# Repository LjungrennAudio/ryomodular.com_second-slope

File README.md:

# ryomodular.com_second-slope
 a peak/trough-analog min/median/max module...

2408310019

this is a slightly interesting one - clearly this started as two separate module and then got cobbled together into abit of a monster but i suspect its got more legs yet and could really turn into something even more original and special.

it seems to consist of a min/median/max module - asolute classic analog logic tool a nd stalwart feature of any good patch programmable system - but nailed on the end is a peak/trough detector with a noice feature set of rising/falling/steady/moving outs.
it's definitely got legs as something but i'd like to find a away to make it far more unique and intersting than just plain old analog logic basics as is.
it's yet another candidate wth high possibilities as part of the jacob's ladder projecgt but i don't know if there's room fo all the functionality this offers in such a mdoule as that.

we'll have to watch and wait with baited breath, eh?

#######

2409060303

see jacob's ladder for continuation.

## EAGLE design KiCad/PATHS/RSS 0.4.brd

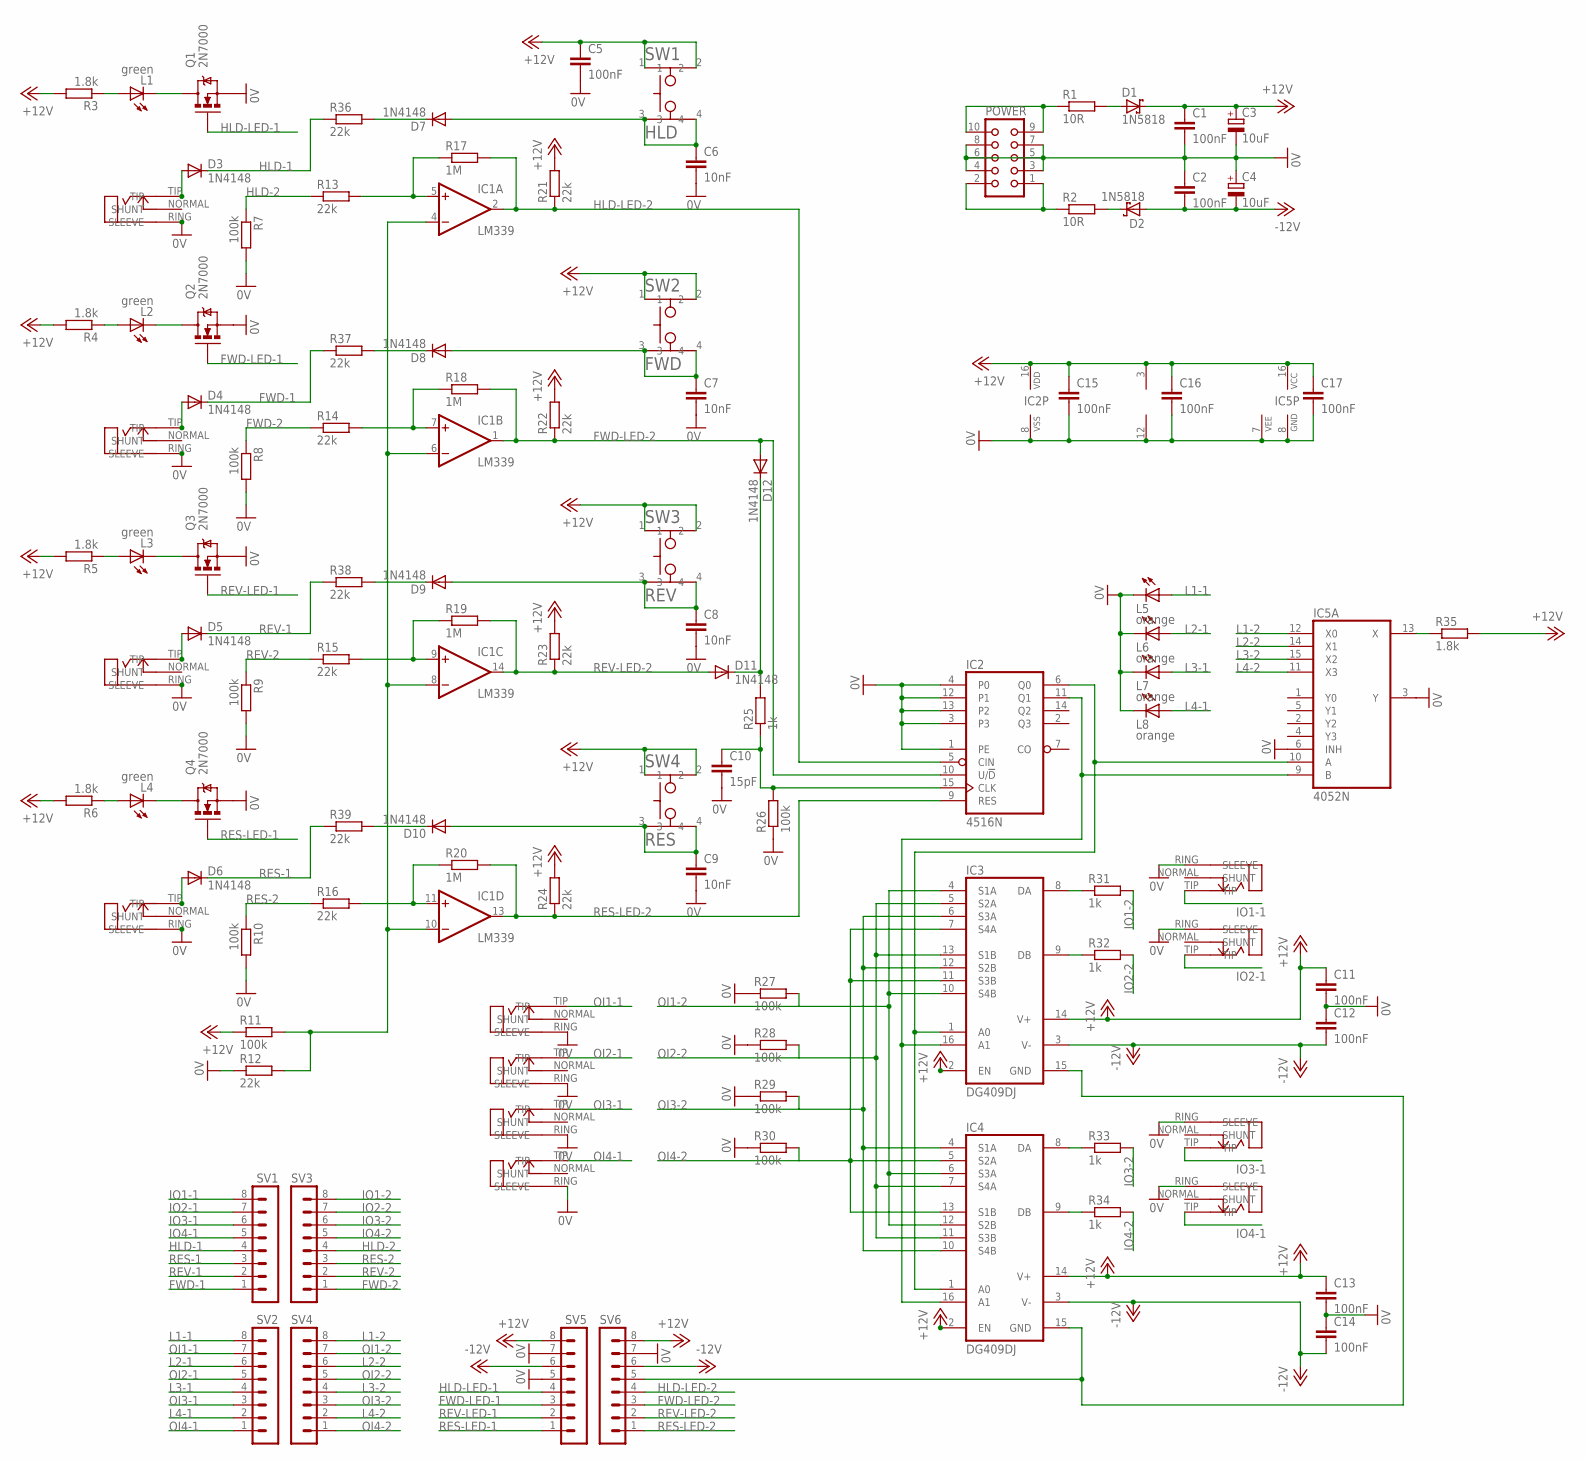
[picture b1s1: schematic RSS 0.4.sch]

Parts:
C1, C2, C5, C11, C12, C13, C14, C15, C16, C17: 100nF; C025-024X044
C3, C4: 10uF; E2-5
C6, C7, C8, C9: 10nF; C025-024X044
C10: 15pF; C025-024X044
D1, D2: 1N5818; DO41-7
D3, D4, D5, D6, D7, D8, D9, D10, D11, D12: 1N4148; DO35-7
FWD: ERTHENVAR_3.5MM_JACK; THONKICON
HLD: ERTHENVAR_3.5MM_JACK; THONKICON
I/O1, I/O2, I/O3, I/O4: ERTHENVAR_3.5MM_JACK; THONKICON
IC1: LM339; DIL14
IC2: 4516N; DIL16
IC3, IC4: DG409DJ; DIL16
IC5: 4052N; DIL16
L1, L2, L3, L4: green; LED3MM
L5, L6, L7, L8: orange; LED3MM
O/I1, O/I2, O/I3, O/I4: ERTHENVAR_3.5MM_JACK; THONKICON
POWER: CON10L
Q1, Q2, Q3, Q4: 2N7000; TO92-LINE
R1, R2: 10R; 0207/9
R3, R4, R5, R6, R35: 1.8k; 0207/9
R7, R8, R9, R10, R11, R26, R27, R28, R29, R30: 100k; 0207/9
R12, R13, R14, R15, R16, R21, R22, R23, R24, R36, R37, R38, R39: 22k; 0207/9
R17, R18, R19, R20: 1M; 0207/9
R25, R31, R32, R33, R34: 1k; 0207/9
RES: ERTHENVAR_3.5MM_JACK; THONKICON
REV: ERTHENVAR_3.5MM_JACK; THONKICON
SV1, SV2, SV3, SV4, SV5, SV6: MA08-1
SW1: HLD; TACTILE_ALPS
SW2: FWD; TACTILE_ALPS
SW3: REV; TACTILE_ALPS
SW4: RES; TACTILE_ALPS

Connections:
0V: C1.2, C2.1, C3.-, C4.+, C5.2, C6.2, C7.2, C8.2, C9.2, C10.2, C11.2, C12.1, C13.2, C14.1, C15.2, C16.2, C17.2, FWD.RING (SLEEVE), HLD.RING (SLEEVE), I/O1.RING (SLEEVE), I/O2.RING (SLEEVE), I/O3.RING (SLEEVE), I/O4.RING (SLEEVE), IC1.12 (V-), IC2.1 (PE), IC2.3, IC2.4 (P0), IC2.8 (VSS), IC2.12 (P1), IC2.13 (P2), IC5.3 (Y), IC5.6 (INH), IC5.7 (VEE), IC5.8 (GND), L5.K (C), L6.K (C), L7.K (C), L8.K (C), O/I1.RING (SLEEVE), O/I2.RING (SLEEVE), O/I3.RING (SLEEVE), O/I4.RING (SLEEVE), POWER.3, POWER.4, POWER.5, POWER.6, POWER.7, POWER.8, Q1.3 (S), Q2.3 (S), Q3.3 (S), Q4.3 (S), R7.2, R8.2, R9.2, R10.2, R12.1, R26.1, R27.1, R28.1, R29.1, R30.1, RES.RING (SLEEVE), REV.RING (SLEEVE), SV5.5, SV5.7, SV6.7
+12V: C1.1, C3.+, C5.1, C11.1, C13.1, C15.1, C16.1, C17.1, D1.C, IC1.3 (V+), IC2.16 (VDD), IC3.2 (EN), IC3.14 (V+), IC4.2 (EN), IC4.14 (V+), IC5.16 (VCC), R3.2, R4.2, R5.2, R6.2, R11.1, R21.2, R22.2, R23.2, R24.2, R35.2, SV5.8, SV6.8, SW1.1, SW1.2, SW2.1, SW2.2, SW3.1, SW3.2, SW4.1, SW4.2
-12V: C2.2, C4.-, C12.2, C14.2, D2.A, IC3.3 (V-), IC4.3 (V-), SV5.6, SV6.6
FWD-1: D4.C, R37.1, SV1.1
FWD-2: R8.1, R14.1, SV3.1
FWD-LED-1: Q2.2 (G), SV5.3
FWD-LED-2: D12.A, IC1.1 (OUT), IC2.10 (U/!D), R18.2, R22.1, SV6.3
HLD-1: D3.C, R36.1, SV1.4
HLD-2: R7.1, R13.1, SV3.4
HLD-LED-1: Q1.2 (G), SV5.4
HLD-LED-2: IC1.2 (OUT), IC2.5 (CIN), R17.2, R21.1, SV6.4
IO1-1: I/O1.TIP, SV1.8
IO1-2: R31.2, SV3.8
IO2-1: I/O2.TIP, SV1.7
IO2-2: R32.2, SV3.7
IO3-1: I/O3.TIP, SV1.6
IO3-2: R33.2, SV3.6
IO4-1: I/O4.TIP, SV1.5
IO4-2: R34.2, SV3.5
L1-1: L5.A, SV2.8
L1-2: IC5.12 (X0), SV4.8
L2-1: L6.A, SV2.6
L2-2: IC5.14 (X1), SV4.6
L3-1: L7.A, SV2.4
L3-2: IC5.15 (X2), SV4.4
L4-1: L8.A, SV2.2
L4-2: IC5.11 (X3), SV4.2
unnamed: IC2.11 (Q1), IC3.16 (A1), IC4.16 (A1), IC5.9 (B)
unnamed: IC2.6 (Q0), IC3.1 (A0), IC4.1 (A0), IC5.10 (A)
unnamed: IC3.15 (GND), IC4.15 (GND), SV6.5
unnamed: C10.1, IC2.15 (CLK), R25.1, R26.2
unnamed: IC3.9 (DB), R32.1
unnamed: IC4.9 (DB), R34.1
unnamed: L2.A, R4.1
unnamed: D3.A, HLD.TIP
unnamed: IC4.8 (DA), R33.1
unnamed: D4.A, FWD.TIP
unnamed: D5.A, REV.TIP
unnamed: D6.A, RES.TIP
unnamed: IC3.8 (DA), R31.1
unnamed: L2.K (C), Q2.1 (D)
unnamed: L3.A, R5.1
unnamed: C7.1, D8.A, SW2.3, SW2.4
unnamed: L3.K (C), Q3.1 (D)
unnamed: C6.1, D7.A, SW1.3, SW1.4
unnamed: IC5.13 (X), R35.1
unnamed: L4.A, R6.1
unnamed: IC1.7 (+IN), R14.2, R18.1
unnamed: POWER.1, POWER.2, R2.1
unnamed: POWER.9, POWER.10, R1.1
unnamed: D1.A, R1.2
unnamed: D2.C, R2.2
unnamed: IC1.5 (+IN), R13.2, R17.1
unnamed: IC1.9 (+IN), R15.2, R19.1
unnamed: L4.K (C), Q4.1 (D)
unnamed: IC1.4 (-IN), IC1.6 (-IN), IC1.8 (-IN), IC1.10 (-IN), R11.2, R12.2
unnamed: C8.1, D9.A, SW3.3, SW3.4
unnamed: IC1.11 (+IN), R16.2, R20.1
unnamed: C9.1, D10.A, SW4.3, SW4.4
unnamed: D10.C, R39.2
unnamed: D9.C, R38.2
unnamed: D8.C, R37.2
unnamed: D7.C, R36.2
unnamed: D11.C, D12.C, R25.2
unnamed: L1.A, R3.1
unnamed: L1.K (C), Q1.1 (D)
OI1-1: O/I1.TIP, SV2.7
OI1-2: IC3.4 (S1A), IC3.10 (S4B), IC4.6 (S3A), IC4.12 (S2B), R27.2, SV4.7
OI2-1: O/I2.TIP, SV2.5
OI2-2: IC3.5 (S2A), IC3.13 (S1B), IC4.7 (S4A), IC4.11 (S3B), R28.2, SV4.5
OI3-1: O/I3.TIP, SV2.3
OI3-2: IC3.6 (S3A), IC3.12 (S2B), IC4.4 (S1A), IC4.10 (S4B), R29.2, SV4.3
OI4-1: O/I4.TIP, SV2.1
OI4-2: IC3.7 (S4A), IC3.11 (S3B), IC4.5 (S2A), IC4.13 (S1B), R30.2, SV4.1
RES-1: D6.C, R39.1, SV1.3
RES-2: R10.1, R16.1, SV3.3
RES-LED-1: Q4.2 (G), SV5.1
RES-LED-2: IC1.13 (OUT), IC2.9 (RES), R20.2, R24.1, SV6.1
REV-1: D5.C, R38.1, SV1.2
REV-2: R9.1, R15.1, SV3.2
REV-LED-1: Q3.2 (G), SV5.2
REV-LED-2: D11.A, IC1.14 (OUT), R19.2, R23.1, SV6.2

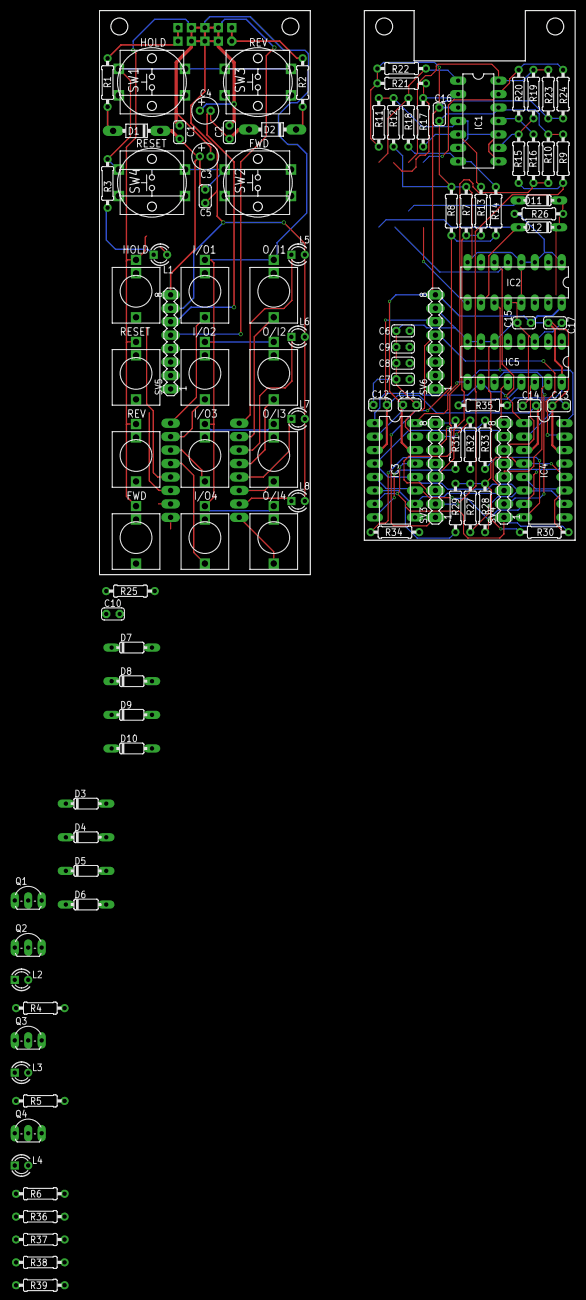
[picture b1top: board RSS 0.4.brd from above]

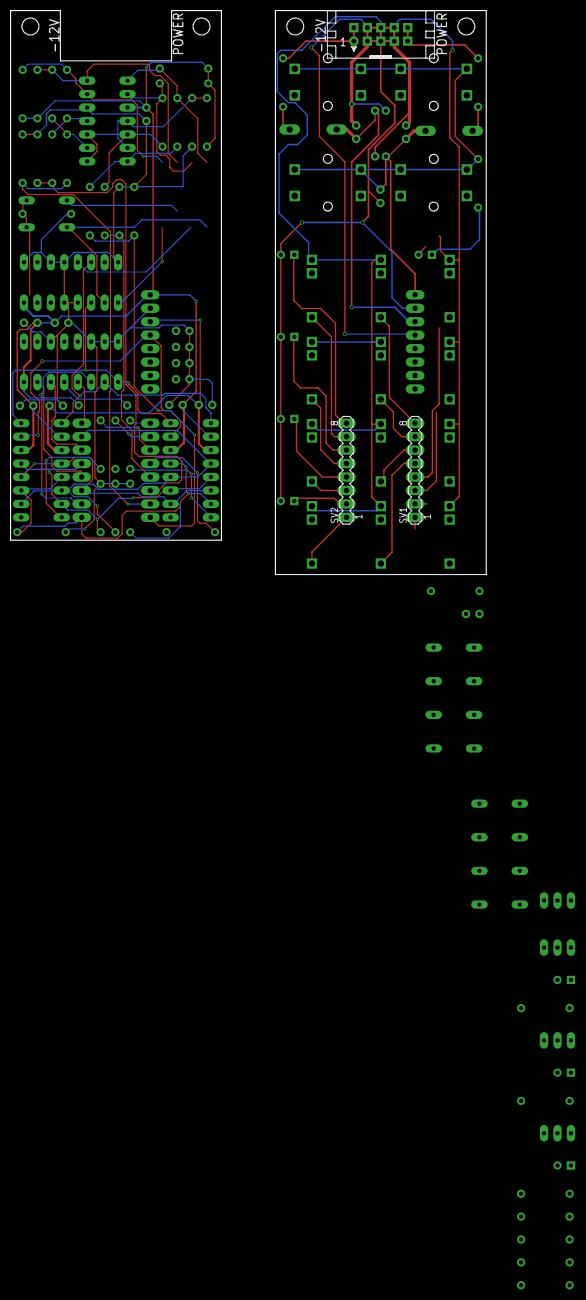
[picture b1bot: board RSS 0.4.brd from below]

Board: 2 copper layers, 89.8 x 106.5 mm, 108 parts (3 on the bottom side), 82 nets.

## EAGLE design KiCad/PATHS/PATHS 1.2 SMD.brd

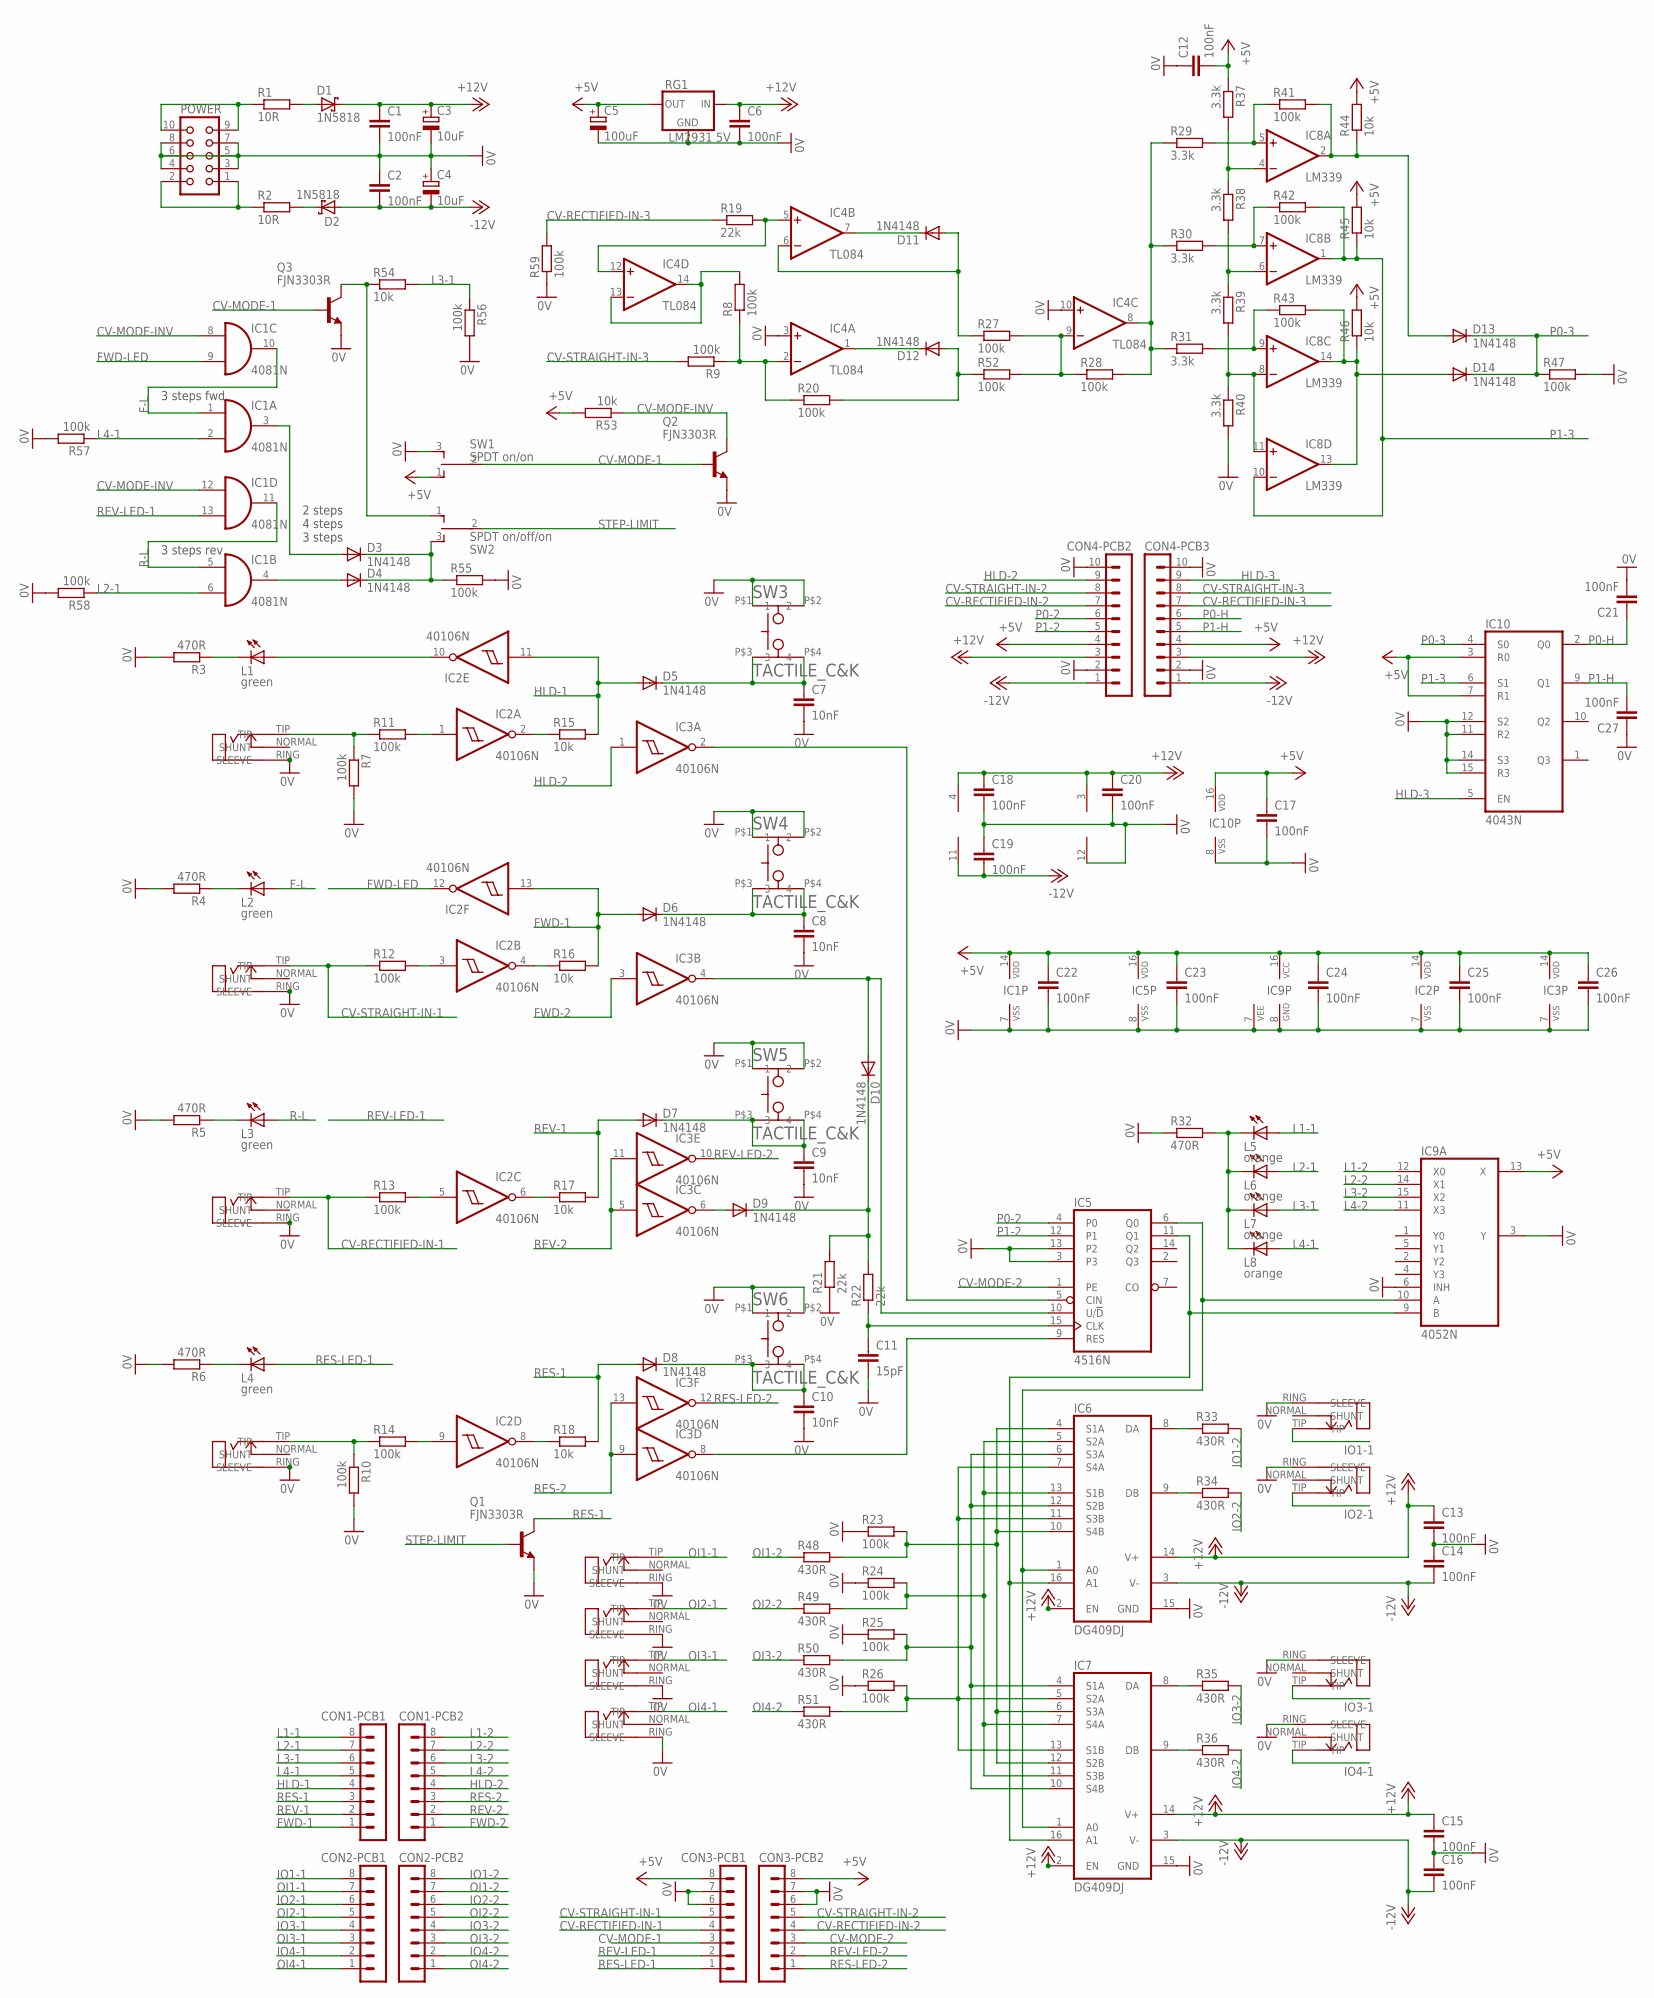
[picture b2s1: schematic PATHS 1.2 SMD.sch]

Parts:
C1, C2, C6, C12, C13, C14, C15, C16, C17, C18, C19, C20, C21, C22, C23, C24, C25, C26, C27: 100nF; C025-024X044
C3, C4: 10uF; E2-5
C5: 100uF; E2,5-6
C7, C8, C9, C10: 10nF; C025-024X044
C11: 15pF; C025-024X044
CON1-PCB1, CON1-PCB2, CON2-PCB1, CON2-PCB2, CON3-PCB1, CON3-PCB2: MA08-1
CON4-PCB2, CON4-PCB3: MA10-1
D1, D2: 1N5818; DO41-7
D3, D4, D5, D6, D7, D8, D9, D10, D11, D12, D13, D14: 1N4148; DO35-6
FWD: ERTHENVAR_3.5MM_JACKINLINE2; THONKICON-TWISTED
HLD: ERTHENVAR_3.5MM_JACKINLINE2; THONKICON-TWISTED
I/O1, I/O2, I/O3, I/O4: ERTHENVAR_3.5MM_JACKINLINE2; THONKICON-TWISTED
IC1: 4081N; DIL14
IC2, IC3: 40106N; DIL14
IC4: TL084; DIL14
IC5: 4516N; DIL16
IC6, IC7: DG409DJ; DIL16
IC8: LM339; DIL14
IC9: 4052N; DIL16
IC10: 4043N; DIL16
L1, L2, L3, L4: green; LED3MM
L5, L6, L7, L8: orange; LED3MM
O/I1, O/I2, O/I3, O/I4: ERTHENVAR_3.5MM_JACKINLINE2; THONKICON-TWISTED
POWER: CON10L
Q1, Q2, Q3: FJN3303R; TO92-LINE
R1, R2: 10R; 0207/9
R3, R4, R5, R6, R32: 470R; 0204/5
R7, R8, R9, R10, R11, R12, R13, R14, R20, R23, R24, R25, R26, R27, R28, R41, R42, R43, R47, R52, R55, R56, R57, R58, R59: 100k; 0204/5
R15, R16, R17, R18, R44, R45, R46, R53, R54: 10k; 0204/5
R19, R21, R22: 22k; 0204/5
R29, R30, R31, R37, R38, R39, R40: 3.3k; 0204/5
R33, R34, R35, R36, R48, R49, R50, R51: 430R; 0207/9
RES: ERTHENVAR_3.5MM_JACKINLINE2; THONKICON-TWISTED
REV: ERTHENVAR_3.5MM_JACKINLINE2; THONKICON-TWISTED
RG1: LM2931 5V; TO92-LINE
SW1: SPDT on/on; SPDT-HORIZONTAL-TOP-SUBMINI-MULTICOMP
SW2: SPDT on/off/on; SPDT-HORIZONTAL-TOP-SUBMINI-MULTICOMP
SW3, SW4, SW5, SW6: TACTILE_C&K; TACTILE_CK

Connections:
0V: C1.2, C2.1, C3.-, C4.+, C5.-, C6.2, C7.2, C8.2, C9.2, C10.2, C11.2, C12.1, C13.2, C14.1, C15.2, C16.1, C17.2, C18.2, C19.1, C20.2, C21.2, C22.2, C23.2, C24.2, C25.2, C26.2, C27.1, CON3-PCB1.6, CON3-PCB1.7, CON3-PCB2.6, CON3-PCB2.7, CON4-PCB2.2, CON4-PCB2.10, CON4-PCB3.2, CON4-PCB3.10, FWD.RING (SLEEVE), HLD.RING (SLEEVE), I/O1.RING (SLEEVE), I/O2.RING (SLEEVE), I/O3.RING (SLEEVE), I/O4.RING (SLEEVE), IC1.7 (VSS), IC2.7 (VSS), IC3.7 (VSS), IC4.3 (+IN), IC4.10 (+IN), IC5.3, IC5.8 (VSS), IC5.13 (P2), IC6.15 (GND), IC7.15 (GND), IC8.12 (V-), IC9.3 (Y), IC9.6 (INH), IC9.7 (VEE), IC9.8 (GND), IC10.8 (VSS), IC10.11 (R2), IC10.12 (S2), IC10.14 (S3), IC10.15 (R3), O/I1.RING (SLEEVE), O/I2.RING (SLEEVE), O/I3.RING (SLEEVE), O/I4.RING (SLEEVE), POWER.3, POWER.4, POWER.5, POWER.6, POWER.7, POWER.8, Q1.3 (E), Q2.3 (E), Q3.3 (E), R3.2, R4.2, R5.2, R6.2, R7.2, R10.2, R21.1, R23.1, R24.1, R25.1, R26.1, R32.1, R40.2, R47.2, R55.2, R56.2, R57.2, R58.2, R59.1, RES.RING (SLEEVE), REV.RING (SLEEVE), RG1.2 (GND), SW1.3, SW3.P$1 (1), SW3.P$2 (2), SW4.P$1 (1), SW4.P$2 (2), SW5.P$1 (1), SW5.P$2 (2), SW6.P$1 (1), SW6.P$2 (2)
+5V: C5.+, C12.2, C17.1, C22.1, C23.1, C24.1, C25.1, C26.1, CON3-PCB1.8, CON3-PCB2.8, CON4-PCB2.4, CON4-PCB3.4, IC1.14 (VDD), IC2.14 (VDD), IC3.14 (VDD), IC5.16 (VDD), IC9.13 (X), IC9.16 (VCC), IC10.3 (R0), IC10.7 (R1), IC10.16 (VDD), R37.1, R44.2, R45.2, R46.2, R53.2, RG1.3 (OUT), SW1.1
+12V: C1.1, C3.+, C6.1, C13.1, C15.1, C18.1, C20.1, CON4-PCB2.3, CON4-PCB3.3, D1.C, IC4.4 (V+), IC6.2 (EN), IC6.14 (V+), IC7.2 (EN), IC7.14 (V+), IC8.3 (V+), RG1.1 (IN)
-12V: C2.2, C4.-, C14.2, C16.2, C19.2, CON4-PCB2.1, CON4-PCB3.1, D2.A, IC4.11 (V-), IC6.3 (V-), IC7.3 (V-)
BDF3R2T: C9.1, D7.CATHODE (C), SW5.P$3 (3), SW5.P$4 (4)
CV-MODE-1: CON3-PCB1.3, Q2.1 (B), Q3.1 (B), SW1.2
CV-MODE-2: CON3-PCB2.3, IC5.1 (PE)
CV-MODE-INV: IC1.8 (I0), IC1.12 (I0), Q2.2 (C), R53.1
CV-RECTIFIED-IN-1: CON3-PCB1.4, R13.1, REV.TIP
CV-RECTIFIED-IN-2: CON3-PCB2.4, CON4-PCB2.7
CV-RECTIFIED-IN-3: CON4-PCB3.7, R19.1, R59.2
CV-STRAIGHT-IN-1: CON3-PCB1.5, FWD.TIP, R12.1
CV-STRAIGHT-IN-2: CON3-PCB2.5, CON4-PCB2.8
CV-STRAIGHT-IN-3: CON4-PCB3.8, R9.2
DFGT43: C8.1, D6.CATHODE (C), SW4.P$3 (3), SW4.P$4 (4)
DVW4D: D9.ANODE (A), IC3.6 (O)
F-L: IC1.1 (I0), IC1.10 (O), L2.A
FGDFS33: IC3.2 (O), IC5.5 (CIN)
FSS44F: IC3.8 (O), IC5.9 (RES)
FWD-1: CON1-PCB1.1, D6.ANODE (A), IC2.13 (I), R16.2
FWD-2: CON1-PCB2.1, IC3.3 (I)
FWD-LED: IC1.9 (I1), IC2.12 (O)
HLD-1: CON1-PCB1.4, D5.ANODE (A), IC2.11 (I), R15.2
HLD-2: CON1-PCB2.4, CON4-PCB2.9, IC3.1 (I)
HLD-3: CON4-PCB3.9, IC10.5 (EN)
IO1-1: CON2-PCB1.8, I/O1.TIP
IO1-2: CON2-PCB2.8, R33.2
IO2-1: CON2-PCB1.6, I/O2.TIP
IO2-2: CON2-PCB2.6, R34.2
IO3-1: CON2-PCB1.4, I/O3.TIP
IO3-2: CON2-PCB2.4, R35.2
IO4-1: CON2-PCB1.2, I/O4.TIP
IO4-2: CON2-PCB2.2, R36.2
L1-1: CON1-PCB1.8, L5.A
L1-2: CON1-PCB2.8, IC9.12 (X0)
L2-1: CON1-PCB1.7, IC1.6 (I1), L6.A, R58.1
L2-2: CON1-PCB2.7, IC9.14 (X1)
L3-1: CON1-PCB1.6, L7.A, R54.2, R56.1
L3-2: CON1-PCB2.6, IC9.15 (X2)
L4-1: CON1-PCB1.5, IC1.2 (I1), L8.A, R57.1
L4-2: CON1-PCB2.5, IC9.11 (X3)
unnamed: IC5.11 (Q1), IC6.16 (A1), IC7.16 (A1), IC9.9 (B)
unnamed: IC5.6 (Q0), IC6.1 (A0), IC7.1 (A0), IC9.10 (A)
unnamed: IC2.3 (I), R12.2
unnamed: C11.1, IC5.15 (CLK), R22.1
unnamed: IC6.9 (DB), R34.1
unnamed: IC7.9 (DB), R36.1
unnamed: L2.K (C), R4.1
unnamed: HLD.TIP, R7.1, R11.1
unnamed: IC7.8 (DA), R35.1
unnamed: IC2.4 (O), R16.1
unnamed: IC2.6 (O), R17.1
unnamed: R10.1, R14.1, RES.TIP
unnamed: IC6.8 (DA), R33.1
unnamed: L1.K (C), R3.1
unnamed: L3.K (C), R5.1
unnamed: IC2.8 (O), R18.1
unnamed: C10.1, D8.CATHODE (C), SW6.P$3 (3), SW6.P$4 (4)
unnamed: IC2.10 (O), L1.A
unnamed: D3.ANODE (A), IC1.3 (O)
unnamed: L4.K (C), R6.1
unnamed: IC2.5 (I), R13.2
unnamed: POWER.1, POWER.2, R2.1
unnamed: POWER.9, POWER.10, R1.1
unnamed: D1.A, R1.2
unnamed: D2.C, R2.2
unnamed: IC2.9 (I), R14.2
unnamed: IC2.2 (O), R15.1
unnamed: C7.1, D5.CATHODE (C), SW3.P$3 (3), SW3.P$4 (4)
unnamed: IC4.2 (-IN), R8.1, R9.1, R20.1
unnamed: D4.ANODE (A), IC1.4 (O)
unnamed: IC8.4 (-IN), R37.2, R38.1
unnamed: IC8.6 (-IN), R38.2, R39.1
unnamed: IC8.8 (-IN), IC8.11 (+IN), R39.2, R40.1
unnamed: D11.ANODE (A), IC4.6 (-IN), R27.1
unnamed: IC8.9 (+IN), R31.2, R43.1
unnamed: IC8.7 (+IN), R30.2, R42.1
unnamed: IC8.5 (+IN), R29.2, R41.1
unnamed: D9.CATHODE (C), D10.CATHODE (C), R21.2, R22.2
unnamed: L5.K (C), L6.K (C), L7.K (C), L8.K (C), R32.2
unnamed: D14.ANODE (A), IC8.13 (OUT), IC8.14 (OUT), R43.2, R46.1
unnamed: IC6.6 (S3A), IC6.12 (S2B), IC7.4 (S1A), IC7.10 (S4B), R25.2, R50.2
unnamed: D13.ANODE (A), IC8.2 (OUT), R41.2, R44.1
unnamed: IC4.5 (+IN), IC4.12 (+IN), R19.2
unnamed: D11.CATHODE (C), IC4.7 (OUT)
unnamed: D3.CATHODE (C), D4.CATHODE (C), R55.1, SW2.3
unnamed: IC6.7 (S4A), IC6.11 (S3B), IC7.5 (S2A), IC7.13 (S1B), R26.2, R51.2
unnamed: IC2.1 (I), R11.2
unnamed: D12.CATHODE (C), IC4.1 (OUT)
unnamed: IC4.9 (-IN), R27.2, R28.1, R52.2
unnamed: IC4.8 (OUT), R28.2, R29.1, R30.1, R31.1
unnamed: IC6.5 (S2A), IC6.13 (S1B), IC7.7 (S4A), IC7.11 (S3B), R24.2, R49.2
unnamed: IC6.4 (S1A), IC6.10 (S4B), IC7.6 (S3A), IC7.12 (S2B), R23.2, R48.2
unnamed: IC4.13 (-IN), IC4.14 (OUT), R8.2
unnamed: D12.ANODE (A), R20.2, R52.1
unnamed: Q3.2 (C), R54.1, SW2.1
OI1-1: CON2-PCB1.7, O/I1.TIP
OI1-2: CON2-PCB2.7, R48.1
OI2-1: CON2-PCB1.5, O/I2.TIP
OI2-2: CON2-PCB2.5, R49.1
OI3-1: CON2-PCB1.3, O/I3.TIP
OI3-2: CON2-PCB2.3, R50.1
OI4-1: CON2-PCB1.1, O/I4.TIP
OI4-2: CON2-PCB2.1, R51.1
P0-2: CON4-PCB2.6, IC5.4 (P0)
P0-3: D13.CATHODE (C), D14.CATHODE (C), IC10.4 (S0), R47.1
P0-H: C21.1, CON4-PCB3.6, IC10.2 (Q0)
P1-2: CON4-PCB2.5, IC5.12 (P1)
P1-3: IC8.1 (OUT), IC8.10 (-IN), IC10.6 (S1), R42.2, R45.1
P1-H: C27.2, CON4-PCB3.5, IC10.9 (Q1)
R-L: IC1.5 (I0), IC1.11 (O), L3.A
RES-1: CON1-PCB1.3, D8.ANODE (A), Q1.2 (C), R18.2
RES-2: CON1-PCB2.3, IC3.9 (I), IC3.13 (I)
RES-LED-1: CON3-PCB1.1, L4.A
RES-LED-2: CON3-PCB2.1, IC3.12 (O)
REV-1: CON1-PCB1.2, D7.ANODE (A), R17.2
REV-2: CON1-PCB2.2, IC3.5 (I), IC3.11 (I)
REV-LED-1: CON3-PCB1.2, IC1.13 (I1)
REV-LED-2: CON3-PCB2.2, IC3.10 (O)
STEP-LIMIT: Q1.1 (B), SW2.2
XBGE4: D10.ANODE (A), IC3.4 (O), IC5.10 (U/!D)

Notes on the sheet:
2 steps 4 steps 3 steps
3 steps fwd
3 steps rev

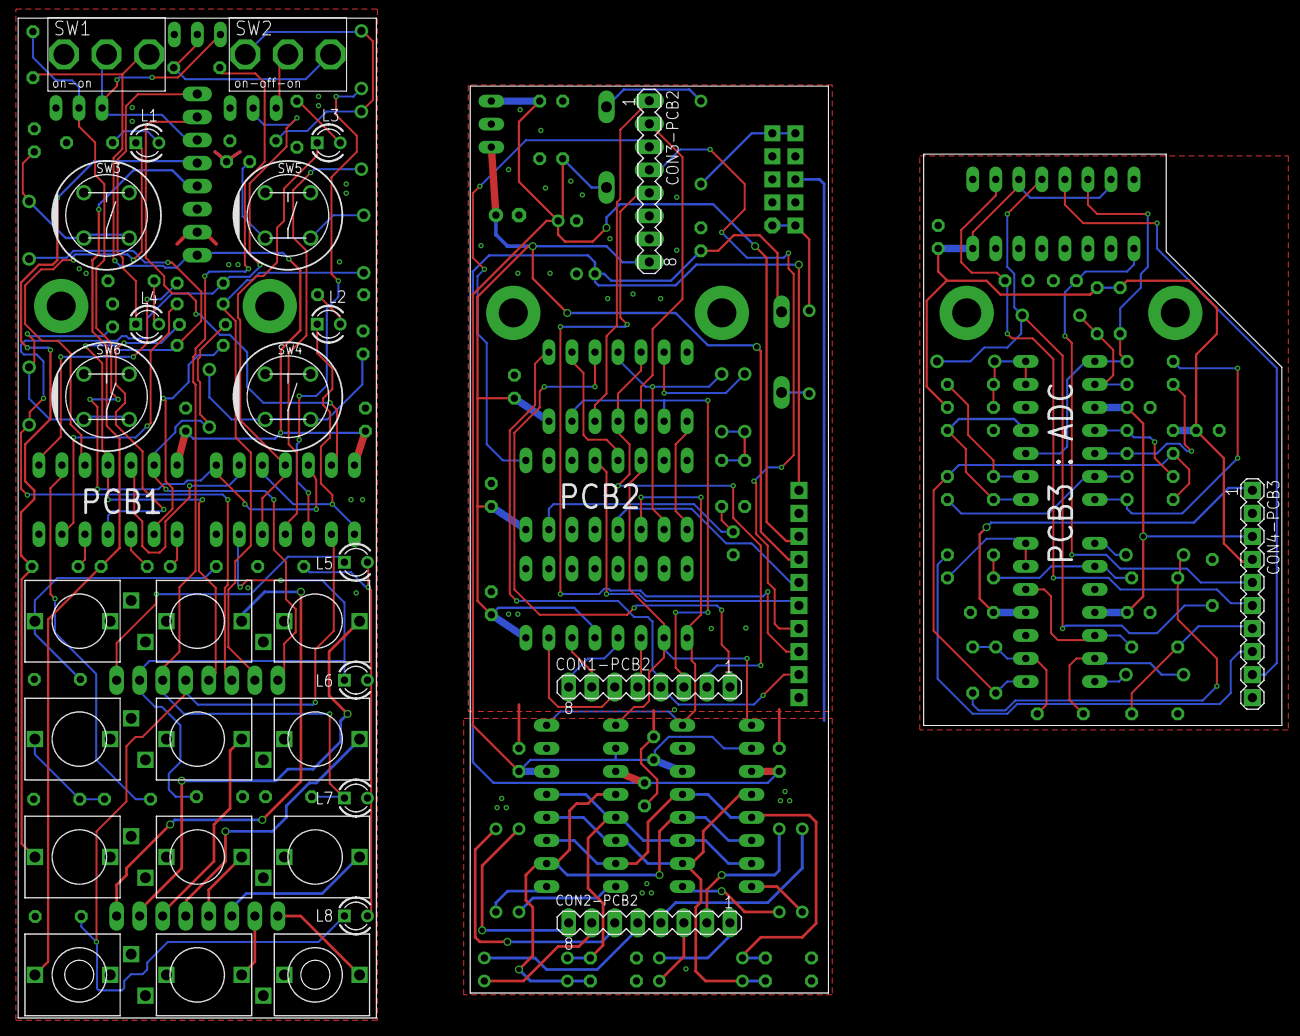
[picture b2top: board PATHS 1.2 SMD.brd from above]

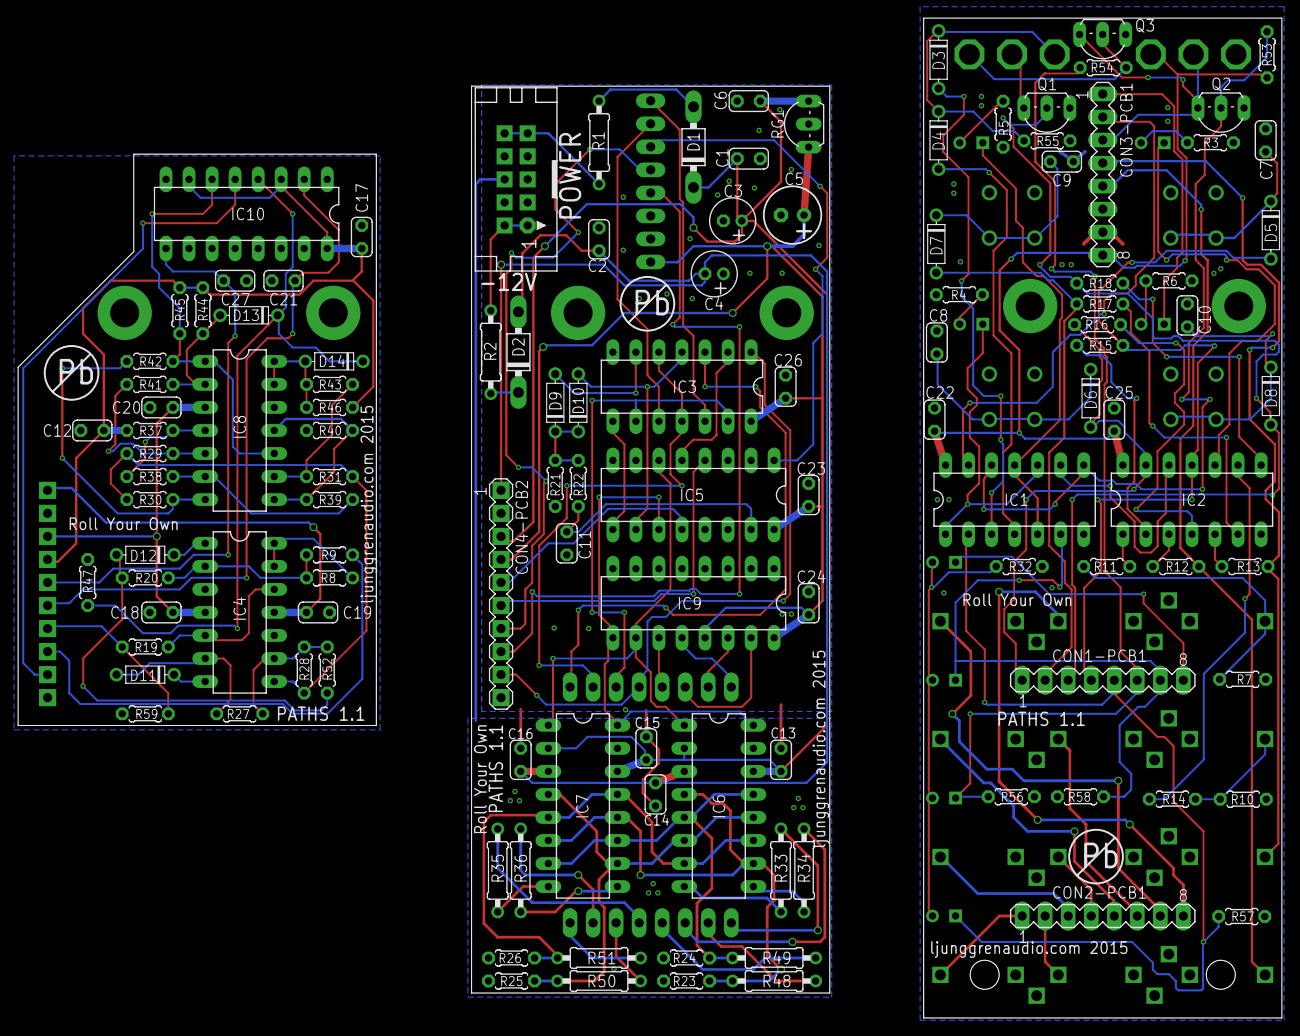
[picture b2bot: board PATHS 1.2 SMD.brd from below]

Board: 2 copper layers, 139.3 x 110.2 mm, 149 parts (119 on the bottom side), 121 nets.

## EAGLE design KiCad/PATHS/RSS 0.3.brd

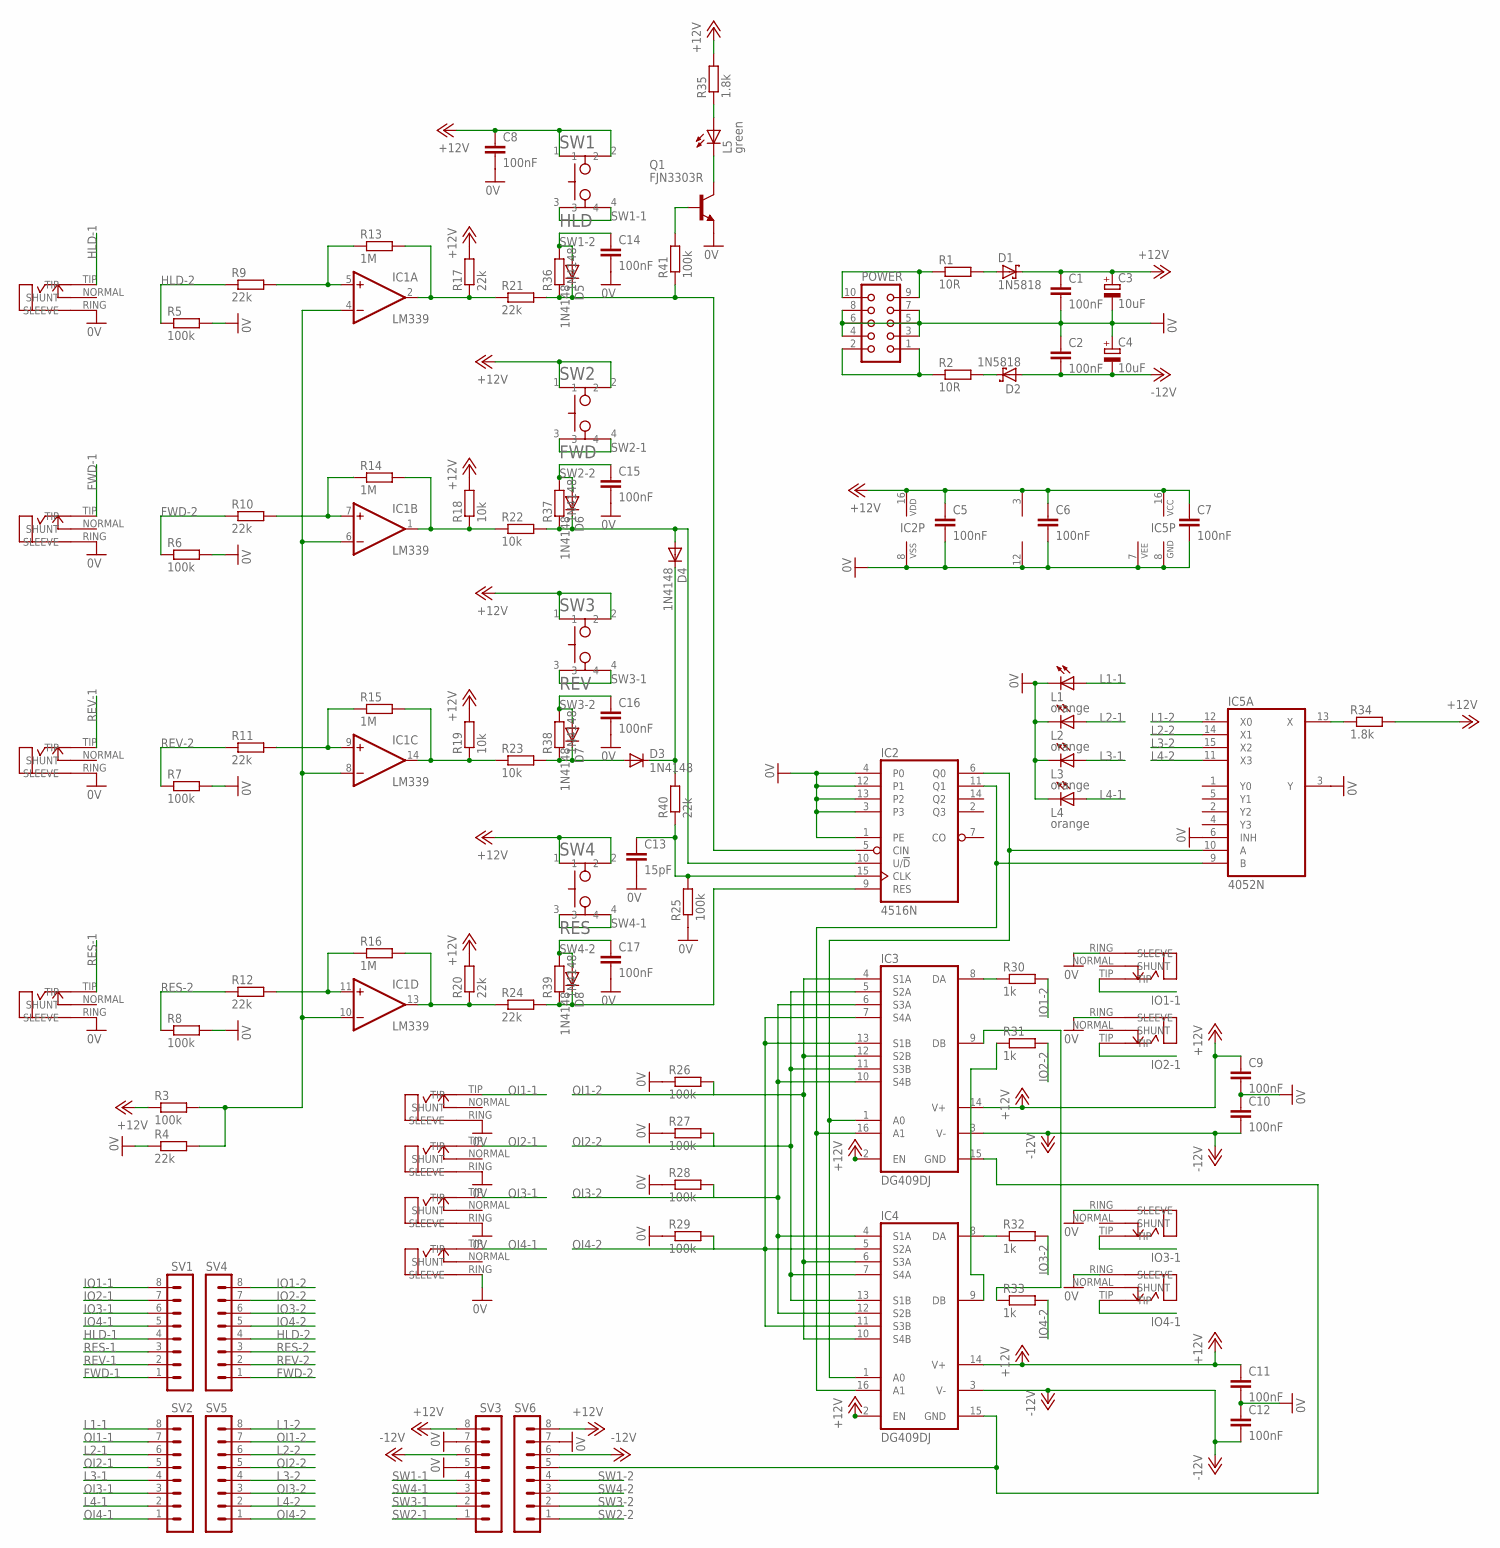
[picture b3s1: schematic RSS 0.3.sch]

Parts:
C1, C2, C5, C6, C7, C8, C9, C10, C11, C12, C14, C15, C16, C17: 100nF; C025-024X044
C3, C4: 10uF; E2-5
C13: 15pF; C025-024X044
D1, D2: 1N5818; DO41-7
D3, D4, D5, D6, D7, D8: 1N4148; DO35-7
FWD: ERTHENVAR_3.5MM_JACK; THONKICON
HLD: ERTHENVAR_3.5MM_JACK; THONKICON
I/O1, I/O2, I/O3, I/O4: ERTHENVAR_3.5MM_JACK; THONKICON
IC1: LM339; DIL14
IC2: 4516N; DIL16
IC3, IC4: DG409DJ; DIL16
IC5: 4052N; DIL16
L1, L2, L3, L4: orange; LED3MM
L5: green; LED3MM
O/I1, O/I2, O/I3, O/I4: ERTHENVAR_3.5MM_JACK; THONKICON
POWER: CON10L
Q1: FJN3303R; TO92-LINE
R1, R2: 10R; 0207/9
R3, R5, R6, R7, R8, R25, R26, R27, R28, R29, R41: 100k; 0207/9
R4, R9, R10, R11, R12, R17, R20, R21, R24, R40: 22k; 0207/9
R13, R14, R15, R16: 1M; 0207/9
R18, R19, R22, R23: 10k; 0207/9
R30, R31, R32, R33: 1k; 0207/9
R34, R35: 1.8k; 0207/9
R36, R37, R38, R39: 1N4148; 0207/9
RES: ERTHENVAR_3.5MM_JACK; THONKICON
REV: ERTHENVAR_3.5MM_JACK; THONKICON
SV1, SV2, SV3, SV4, SV5, SV6: MA08-1
SW1: HLD; TACTILE_ALPS
SW2: FWD; TACTILE_ALPS
SW3: REV; TACTILE_ALPS
SW4: RES; TACTILE_ALPS

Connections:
0V: C1.2, C2.1, C3.-, C4.+, C5.2, C6.2, C7.2, C8.2, C9.2, C10.1, C11.2, C12.1, C13.2, C14.2, C15.2, C16.2, C17.2, FWD.RING (SLEEVE), HLD.RING (SLEEVE), I/O1.RING (SLEEVE), I/O2.RING (SLEEVE), I/O3.RING (SLEEVE), I/O4.RING (SLEEVE), IC1.12 (V-), IC2.1 (PE), IC2.3, IC2.4 (P0), IC2.8 (VSS), IC2.12 (P1), IC2.13 (P2), IC5.3 (Y), IC5.6 (INH), IC5.7 (VEE), IC5.8 (GND), L1.K (C), L2.K (C), L3.K (C), L4.K (C), O/I1.RING (SLEEVE), O/I2.RING (SLEEVE), O/I3.RING (SLEEVE), O/I4.RING (SLEEVE), POWER.3, POWER.4, POWER.5, POWER.6, POWER.7, POWER.8, Q1.3 (E), R4.1, R5.2, R6.2, R7.2, R8.2, R25.1, R26.1, R27.1, R28.1, R29.1, RES.RING (SLEEVE), REV.RING (SLEEVE), SV3.5, SV3.7, SV6.7
+12V: C1.1, C3.+, C5.1, C6.1, C7.1, C8.1, C9.1, C11.1, D1.C, IC1.3 (V+), IC2.16 (VDD), IC3.2 (EN), IC3.14 (V+), IC4.2 (EN), IC4.14 (V+), IC5.16 (VCC), R3.1, R17.2, R18.2, R19.2, R20.2, R34.2, R35.2, SV3.8, SV6.8, SW1.1, SW1.2, SW2.1, SW2.2, SW3.1, SW3.2, SW4.1, SW4.2
-12V: C2.2, C4.-, C10.2, C12.2, D2.A, IC3.3 (V-), IC4.3 (V-), SV3.6, SV6.6
FWD-1: FWD.TIP, SV1.1
FWD-2: R6.1, R10.1, SV4.1
HLD-1: HLD.TIP, SV1.4
HLD-2: R5.1, R9.1, SV4.4
IO1-1: I/O1.TIP, SV1.8
IO1-2: R30.2, SV4.8
IO2-1: I/O2.TIP, SV1.7
IO2-2: R31.2, SV4.7
IO3-1: I/O3.TIP, SV1.6
IO3-2: R32.2, SV4.6
IO4-1: I/O4.TIP, SV1.5
IO4-2: R33.2, SV4.5
L1-1: L1.A, SV2.8
L1-2: IC5.12 (X0), SV5.8
L2-1: L2.A, SV2.6
L2-2: IC5.14 (X1), SV5.6
L3-1: L3.A, SV2.4
L3-2: IC5.15 (X2), SV5.4
L4-1: L4.A, SV2.2
L4-2: IC5.11 (X3), SV5.2
unnamed: IC2.11 (Q1), IC3.16 (A1), IC4.16 (A1), IC5.9 (B)
unnamed: IC2.6 (Q0), IC3.1 (A0), IC4.1 (A0), IC5.10 (A)
unnamed: IC3.15 (GND), IC4.15 (GND), SV6.5
unnamed: C13.1, IC2.15 (CLK), R25.2, R40.1
unnamed: IC3.9 (DB), R33.1
unnamed: IC4.9 (DB), R31.1
unnamed: Q1.1 (B), R41.2
unnamed: IC4.8 (DA), R32.1
unnamed: IC3.8 (DA), R30.1
unnamed: IC1.14 (OUT), R15.2, R19.1, R23.1
unnamed: IC5.13 (X), R34.1
unnamed: D5.C, IC2.5 (CIN), R21.2, R36.1, R41.1
unnamed: IC1.7 (+IN), R10.2, R14.1
unnamed: POWER.1, POWER.2, R2.1
unnamed: POWER.9, POWER.10, R1.1
unnamed: D1.A, R1.2
unnamed: D2.C, R2.2
unnamed: IC1.5 (+IN), R9.2, R13.1
unnamed: IC1.9 (+IN), R11.2, R15.1
unnamed: IC1.2 (OUT), R13.2, R17.1, R21.1
unnamed: IC1.4 (-IN), IC1.6 (-IN), IC1.8 (-IN), IC1.10 (-IN), R3.2, R4.2
unnamed: IC1.11 (+IN), R12.2, R16.1
unnamed: D4.A, D6.C, IC2.10 (U/!D), R22.2, R37.1
unnamed: D8.C, IC2.9 (RES), R24.2, R39.1
unnamed: D3.C, D4.C, R40.2
unnamed: IC1.13 (OUT), R16.2, R20.1, R24.1
unnamed: L5.A, R35.1
unnamed: IC1.1 (OUT), R14.2, R18.1, R22.1
unnamed: L5.K (C), Q1.2 (C)
unnamed: D3.A, D7.C, R23.2, R38.1
OI1-1: O/I1.TIP, SV2.7
OI1-2: IC3.4 (S1A), IC3.12 (S2B), IC4.6 (S3A), IC4.10 (S4B), R26.2, SV5.7
OI2-1: O/I2.TIP, SV2.5
OI2-2: IC3.5 (S2A), IC3.11 (S3B), IC4.7 (S4A), IC4.13 (S1B), R27.2, SV5.5
OI3-1: O/I3.TIP, SV2.3
OI3-2: IC3.6 (S3A), IC3.10 (S4B), IC4.4 (S1A), IC4.12 (S2B), R28.2, SV5.3
OI4-1: O/I4.TIP, SV2.1
OI4-2: IC3.7 (S4A), IC3.13 (S1B), IC4.5 (S2A), IC4.11 (S3B), R29.2, SV5.1
RES-1: RES.TIP, SV1.3
RES-2: R8.1, R12.1, SV4.3
REV-1: REV.TIP, SV1.2
REV-2: R7.1, R11.1, SV4.2
SW1-1: SV3.4, SW1.3, SW1.4
SW1-2: C14.1, D5.A, R36.2, SV6.4
SW2-1: SV3.1, SW2.3, SW2.4
SW2-2: C15.1, D6.A, R37.2, SV6.1
SW3-1: SV3.2, SW3.3, SW3.4
SW3-2: C16.1, D7.A, R38.2, SV6.2
SW4-1: SV3.3, SW4.3, SW4.4
SW4-2: C17.1, D8.A, R39.2, SV6.3

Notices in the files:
parts and their libraries:
SparkFun-DiscreteSemi: Licensing: Creative Commons ShareAlike 4.0 International - https://creativecommons.org/licenses/by-sa/4.0
